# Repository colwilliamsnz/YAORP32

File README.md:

# YAORP32
 
## Yet Another Open Reflow Plate

A design for a solder reflow plate for SMD rework using commonly available aluminium 400W PTC (positive-temperature-coefficient) heating plate from AliExpress. Temperature is
determined using a K type thermocouple and read using a MAX6675/MAX31855. The PTC is driven by an SSR (solid state relay) using PWM and controlled by a PID. An ESP32 S3 Wroom 1 module is at the heart of the design and firmware is written in C++ for Arduino IDE.

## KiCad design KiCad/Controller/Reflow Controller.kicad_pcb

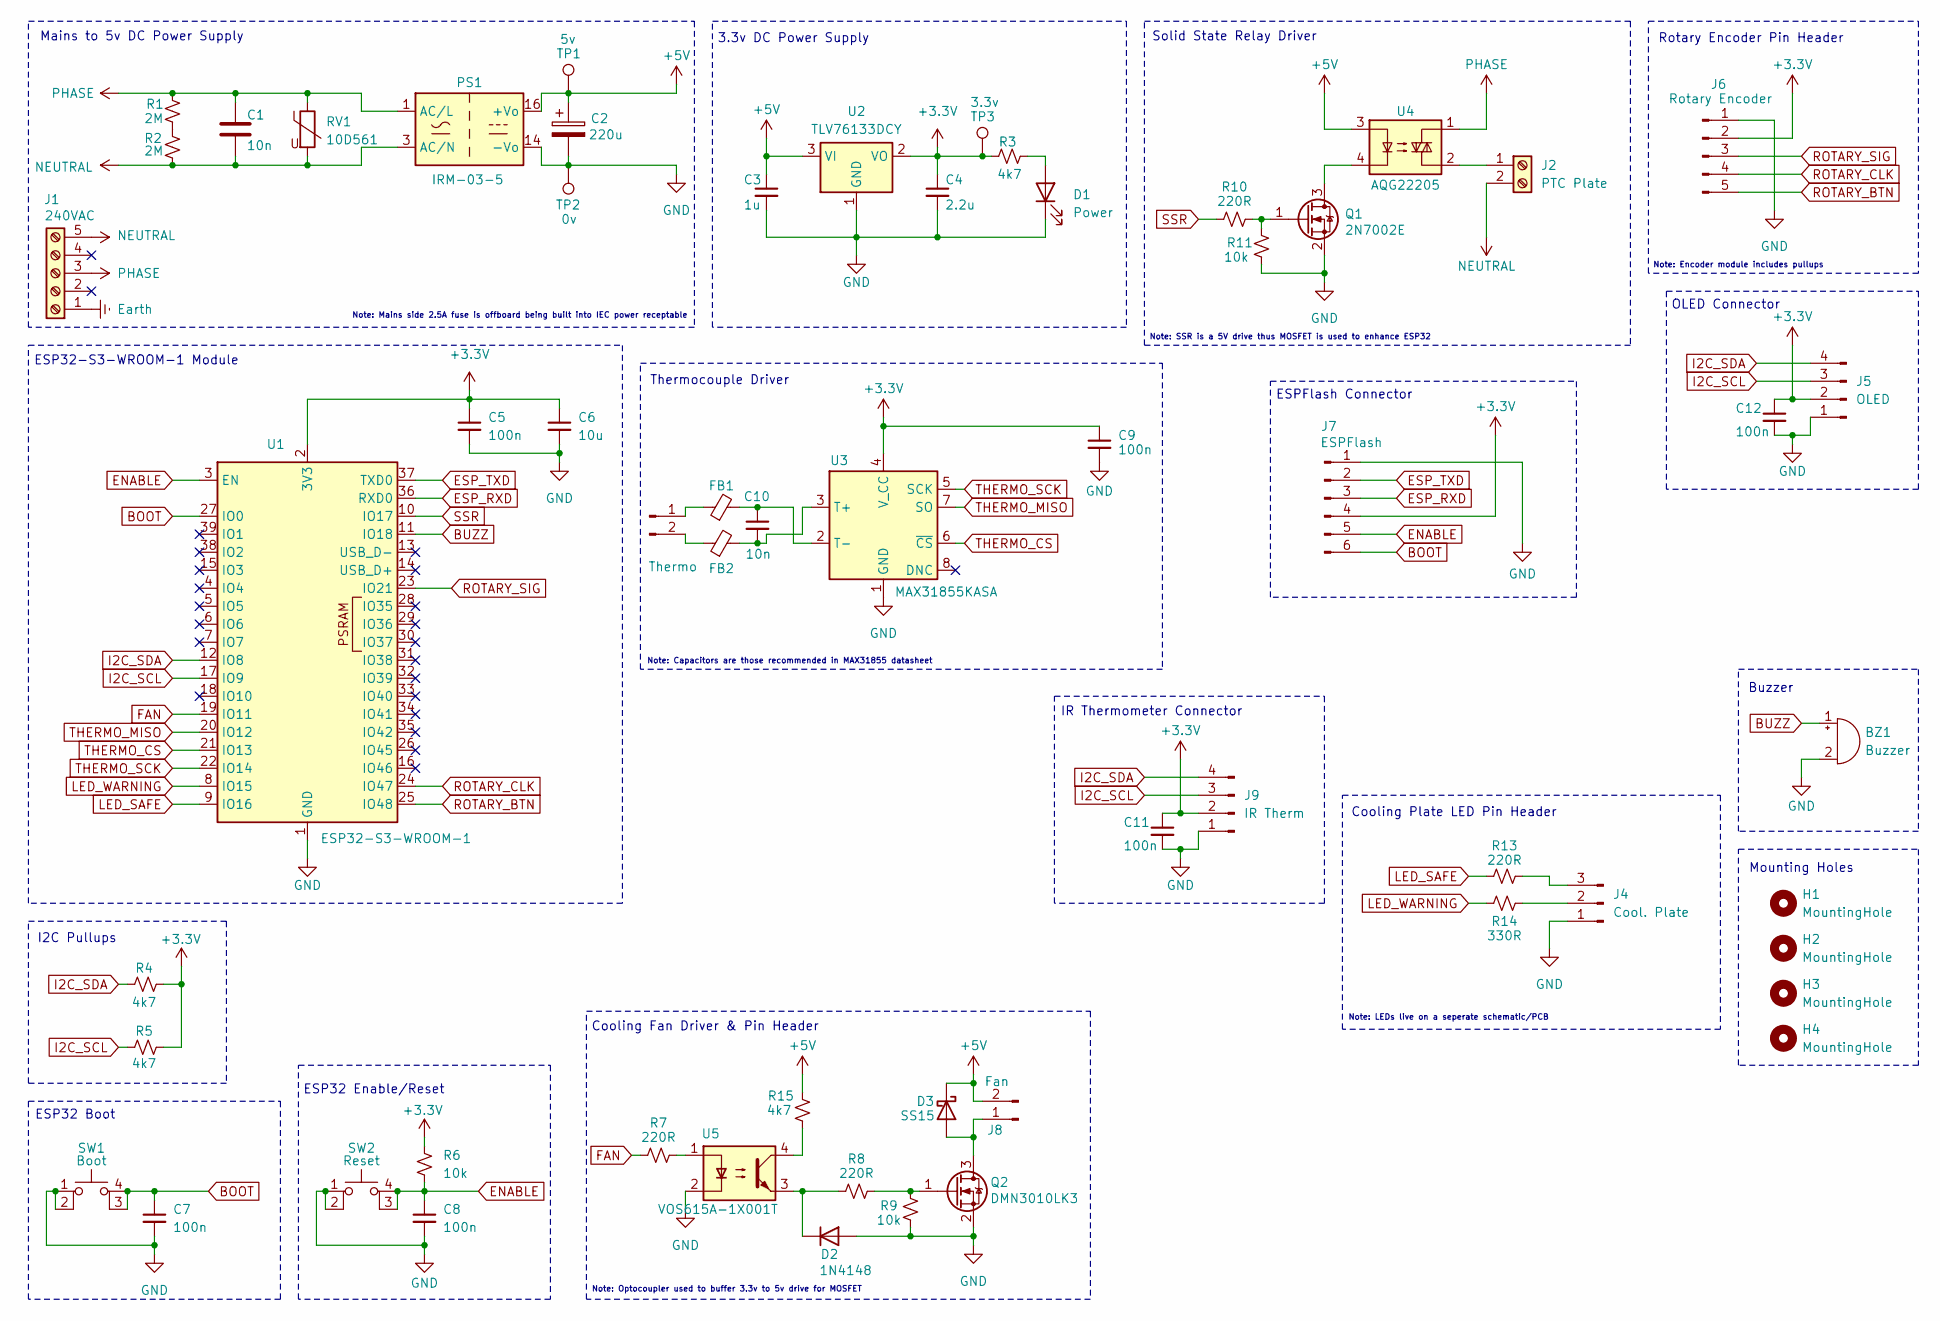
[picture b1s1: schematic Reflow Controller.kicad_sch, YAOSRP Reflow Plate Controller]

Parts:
BZ1: Buzzer; Buzzer_12x9.5RM7.6; Digikey_PN 668-1470-ND
C1: 10n; C_Rect_L18.0mm_W5.0mm_P15.00mm_FKS3_FKP3
C2: 220u; CP_Radial_D6.3mm_P2.50mm
C3: 1u; C_0603_1608Metric; Digikey_PN 1276-1019-1-ND
C4: 2.2u; C_0603_1608Metric; Digikey_PN 1276-1040-1-ND
C5, C7, C8, C9, C11, C12: 100n; C_0603_1608Metric; Digikey_PN 399-C0603C104K4RACTUCT-ND
C6: 10u; C_0805_2012Metric; Digikey_PN 490-6473-1-ND
C10: 10n; C_0603_1608Metric; Digikey_PN 311-3369-1-ND
D1: Power; LED_0603_1608Metric; Digikey_PN 732-4978-1-ND
D2: 1N4148; Nexperia_CFP3_SOD-123W; Digikey_PN 1N4148W-FDICT-ND
D3: SS15; D_SMA; Digikey_PN SS15FSCT-ND
FB1, FB2: 470R 1LN; R_0603_1608Metric; Digikey_PN BLM18PG471SN1D
H1, H2, H3, H4: MountingHole; MountingHole_2.5mm
J1: 240VAC; Altech_AK100_1x05_P5.00mm
J2: PTC Plate; Altech_AK100_1x02_P5.00mm
J3: Thermo; PinHeader_1x02_P2.54mm_Vertical
J4: Cool. Plate; PinHeader_1x03_P2.54mm_Vertical
J5: OLED; PinHeader_1x04_P2.54mm_Vertical
J6: Rotary Encoder; PinHeader_1x05_P2.54mm_Vertical
J7: ESPFlash; PinHeader_1x06_P2.54mm_Vertical
J8: Fan; PinHeader_1x02_P2.54mm_Vertical
J9: IR Therm; PinHeader_1x04_P2.54mm_Vertical
PS1: IRM-03-5; Converter_ACDC_MeanWell_IRM-03-xx_THT; Digikey_PN 1866-3020-ND
Q1: 2N7002E; SOT-23; Digikey_PN 2N7002E-ND
Q2: DMN3010LK3; TO-252-2; Digikey_PN 31-DMN3010LK3-13CT-ND
R1, R2: 2M; R_2010_5025Metric_Pad1.40x2.65mm_HandSolder; Digikey_PN 2019-HV732HTTE2004FCT-ND
R3, R4, R5, R15: 4k7; R_0603_1608Metric_Pad0.98x0.95mm_HandSolder; Digikey_PN 541-3993-1-ND
R6, R9, R11: 10k; R_0603_1608Metric_Pad0.98x0.95mm_HandSolder; Digikey_PN 541-10.0KHCT-ND
R7, R8, R10, R13: 220R; R_0603_1608Metric_Pad0.98x0.95mm_HandSolder; Digikey_PN 541-10440-1-ND
R14: 330R; R_0603_1608Metric_Pad0.98x0.95mm_HandSolder; Digikey_PN 541-10456-1-ND
RV1: 10D561; RV_Disc_D12mm_W6.1mm_P7.5mm; Digikey_PN 118-MOV-10D561K-ND
SW1: Boot; SW_SPST_PTS810; Digikey_PN CKN10878CT-ND
SW2: Reset; SW_SPST_PTS810; Digikey_PN CKN10878CT-ND
TP1: 5v; TestPoint_Pad_D1.0mm
TP2: 0v; TestPoint_Pad_D1.0mm
TP3: 3.3v; TestPoint_Pad_D1.0mm
U1: ESP32-S3-WROOM-1; Digikey_PN 1965-ESP32-S3-WROOM-1-N4R2CT-ND
U2: TLV76133DCY; SOT-223-3_TabPin2; Digikey_PN 296-TLV76133DCYRCT-ND
U3: MAX31855KASA; SOIC-8_3.9x4.9mm_P1.27mm; Digikey_PN MAX31855KASA+-ND
U4: AQG22205; SSR_AQG22105; Digikey_PN 255-3752-ND
U5: VOS615A-1X001T; SSOP-4_4.4x2.6mm_P1.27mm; Digikey_PN 751-VOS615A-1X001TCT-ND

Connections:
+3.3V: C4.1, C5.1, C6.1, C9.1, C11.1, C12.1, J5.2, J6.2, J7.4, J9.2, R3.1, R4.1, R5.1, R6.2, TP3.1, U1.2 (3V3), U2.2 (VO), U3.4 (V_CC)
+5V: C2.1, C3.1, D3.1 (K), J8.2, PS1.16 (+Vo), R15.1, TP1.1, U2.3 (VI), U4.3
BOOT: C7.1, J7.6, SW1.3 (K), SW1.4 (A), U1.27 (IO0)
BUZZ: BZ1.1 (+), U1.11 (IO18)
ENABLE: C8.1, J7.5, R6.1, SW2.3 (K), SW2.4 (A), U1.3 (EN)
ESP_RXD: J7.3, U1.36 (RXD0)
ESP_TXD: J7.2, U1.37 (TXD0)
Earth: J1.1
FAN: R7.2, U1.19 (IO11)
GND: BZ1.2 (-), C2.2, C3.2, C4.2, C5.2, C6.2, C7.2, C8.2, C9.2, C11.2, C12.2, D1.1 (K), D2.2 (A), J4.1, J5.1, J6.1, J7.1, J9.1, PS1.14 (-Vo), Q1.2 (S), Q2.2 (S), R9.2, R11.2, SW1.1, SW1.2, SW2.1, SW2.2, TP2.1, U1.1 (GND), U1.40 (GND), U1.41 (GND), U2.1 (GND), U3.1 (GND), U5.2
I2C_SCL: J5.3, J9.3, R5.2, U1.17 (IO9)
I2C_SDA: J5.4, J9.4, R4.2, U1.12 (IO8)
LED_SAFE: R13.2, U1.9 (IO16)
LED_WARNING: R14.2, U1.8 (IO15)
NEUTRAL: C1.2, J1.5, J2.2, PS1.3 (AC/N), R2.2, RV1.2
unnamed: D1.2 (A), R3.2
unnamed: D2.1 (K), R8.2, U5.3
unnamed: D3.2 (A), J8.1, Q2.3 (D)
unnamed: J2.1, U4.2
unnamed: FB1.1, J3.1
unnamed: FB2.1, J3.2
unnamed: J4.2, R14.1
unnamed: J4.3, R13.1
unnamed: Q1.3 (D), U4.4
unnamed: Q1.1 (G), R10.1, R11.1
unnamed: Q2.1 (G), R8.1, R9.1
unnamed: R1.2, R2.1
unnamed: R7.1, U5.1
unnamed: R15.2, U5.4
unnamed: C10.2, FB2.2, U3.3 (T+)
unnamed: C10.1, FB1.2, U3.2 (T-)
PHASE: C1.1, J1.3, PS1.1 (AC/L), R1.1, RV1.1, U4.1
ROTARY_BTN: J6.5, U1.25 (IO48)
ROTARY_CLK: J6.4, U1.24 (IO47)
ROTARY_SIG: J6.3, U1.23 (IO21)
SSR: R10.2, U1.10 (IO17)
THERMO_CS: U1.21 (IO13), U3.6 (~CS)
THERMO_MISO: U1.20 (IO12), U3.7 (SO)
THERMO_SCK: U1.22 (IO14), U3.5 (SCK)

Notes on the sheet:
Cooling Fan Driver & Pin Header
Thermocouple Driver
Solid State Relay Driver
ESP32 Boot
Buzzer
Note: Capacitors are those recommended in MAX31855 datasheet
Rotary Encoder Pin Header
3.3v DC Power Supply
Note: Optocoupler used to buffer 3.3v to 5v drive for MOSFET
ESP32-S3-WROOM-1 Module
I2C Pullups
ESPFlash Connector
Note: SSR is a 5V drive thus MOSFET is used to enhance ESP32
ESP32 Enable/Reset
Mounting Holes
Note: Mains side 2.5A fuse is offboard being built into IEC power receptable
Mains to 5v DC Power Supply
Cooling Plate LED Pin Header
Note: LEDs live on a seperate schematic/PCB
Note: Encoder module includes pullups
OLED Connector
IR Thermometer Connector

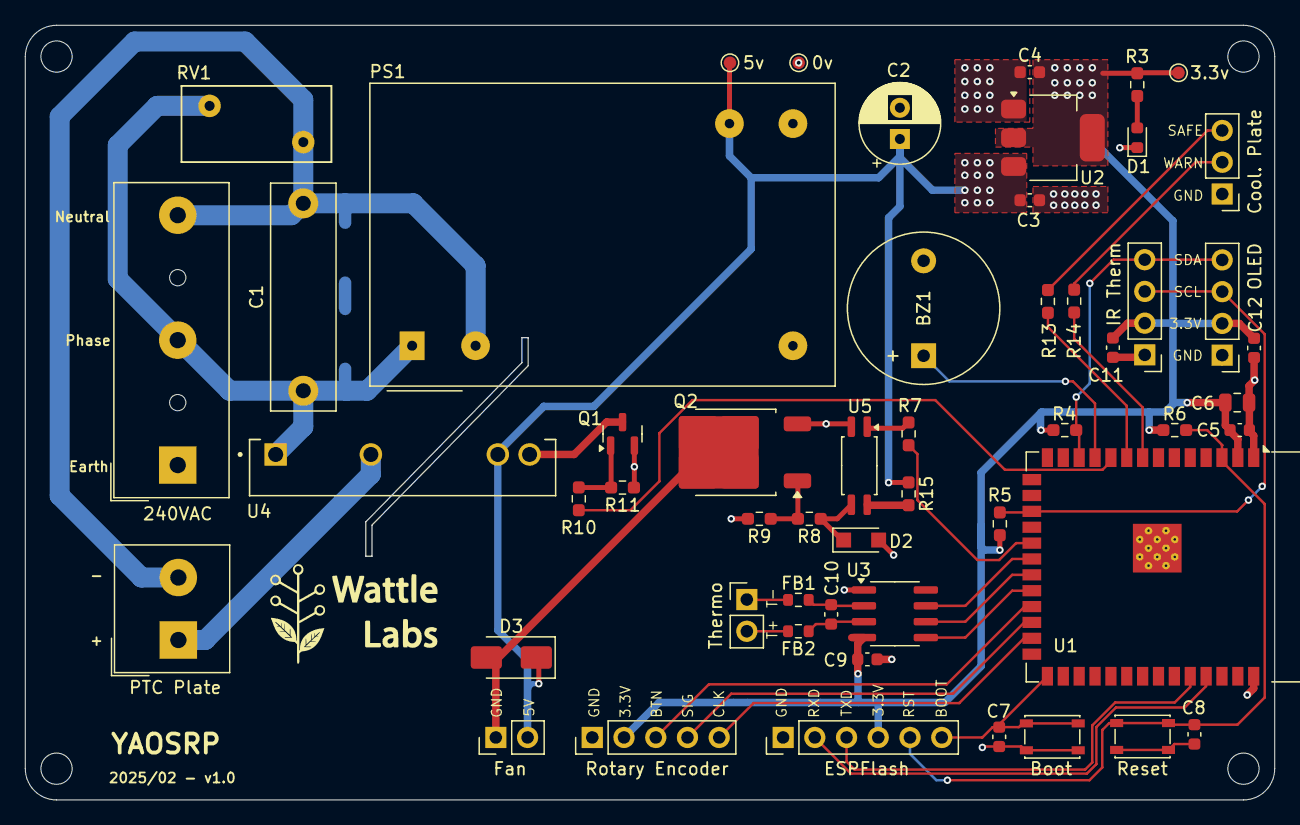
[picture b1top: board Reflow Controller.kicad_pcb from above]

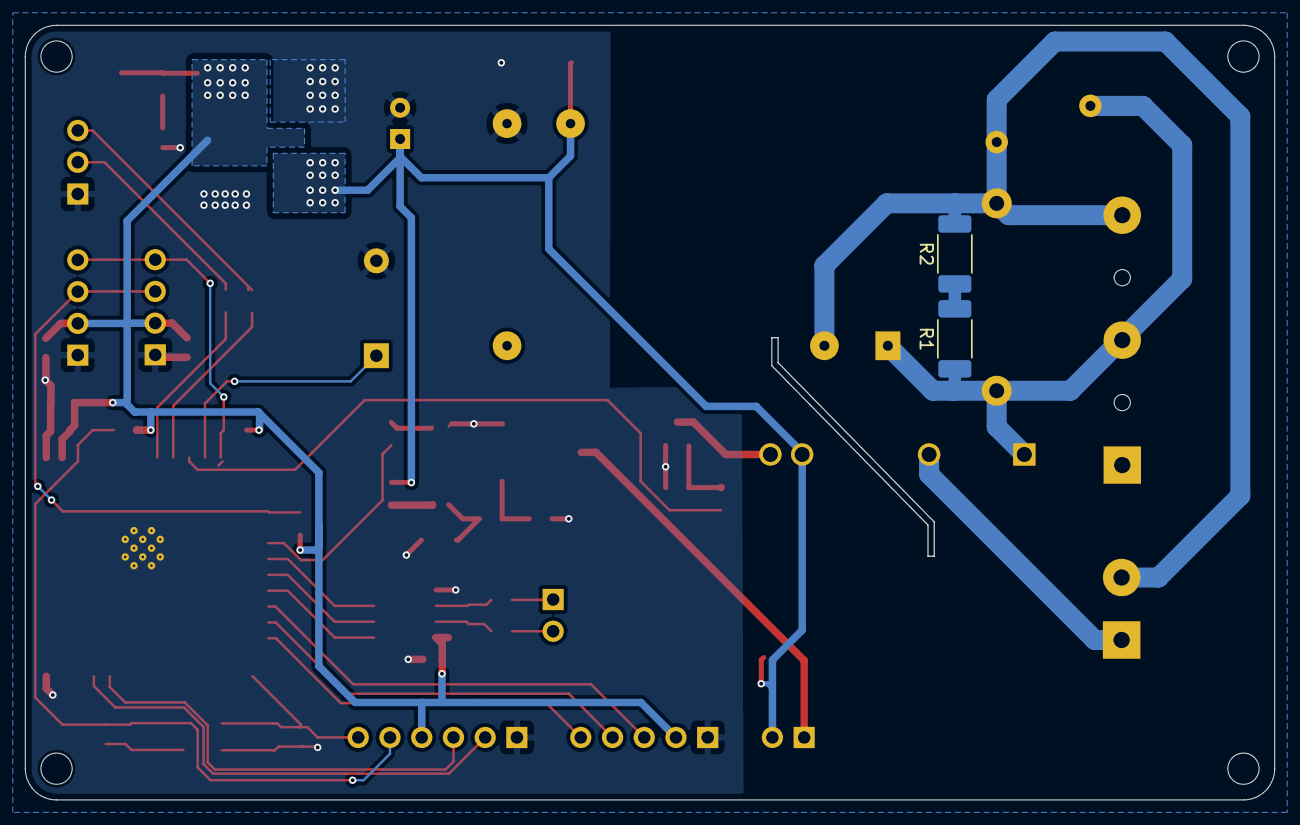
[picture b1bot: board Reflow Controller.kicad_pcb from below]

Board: 4 copper layers, 100.0 x 62.0 mm, 59 parts (2 on the bottom side), 38 nets.

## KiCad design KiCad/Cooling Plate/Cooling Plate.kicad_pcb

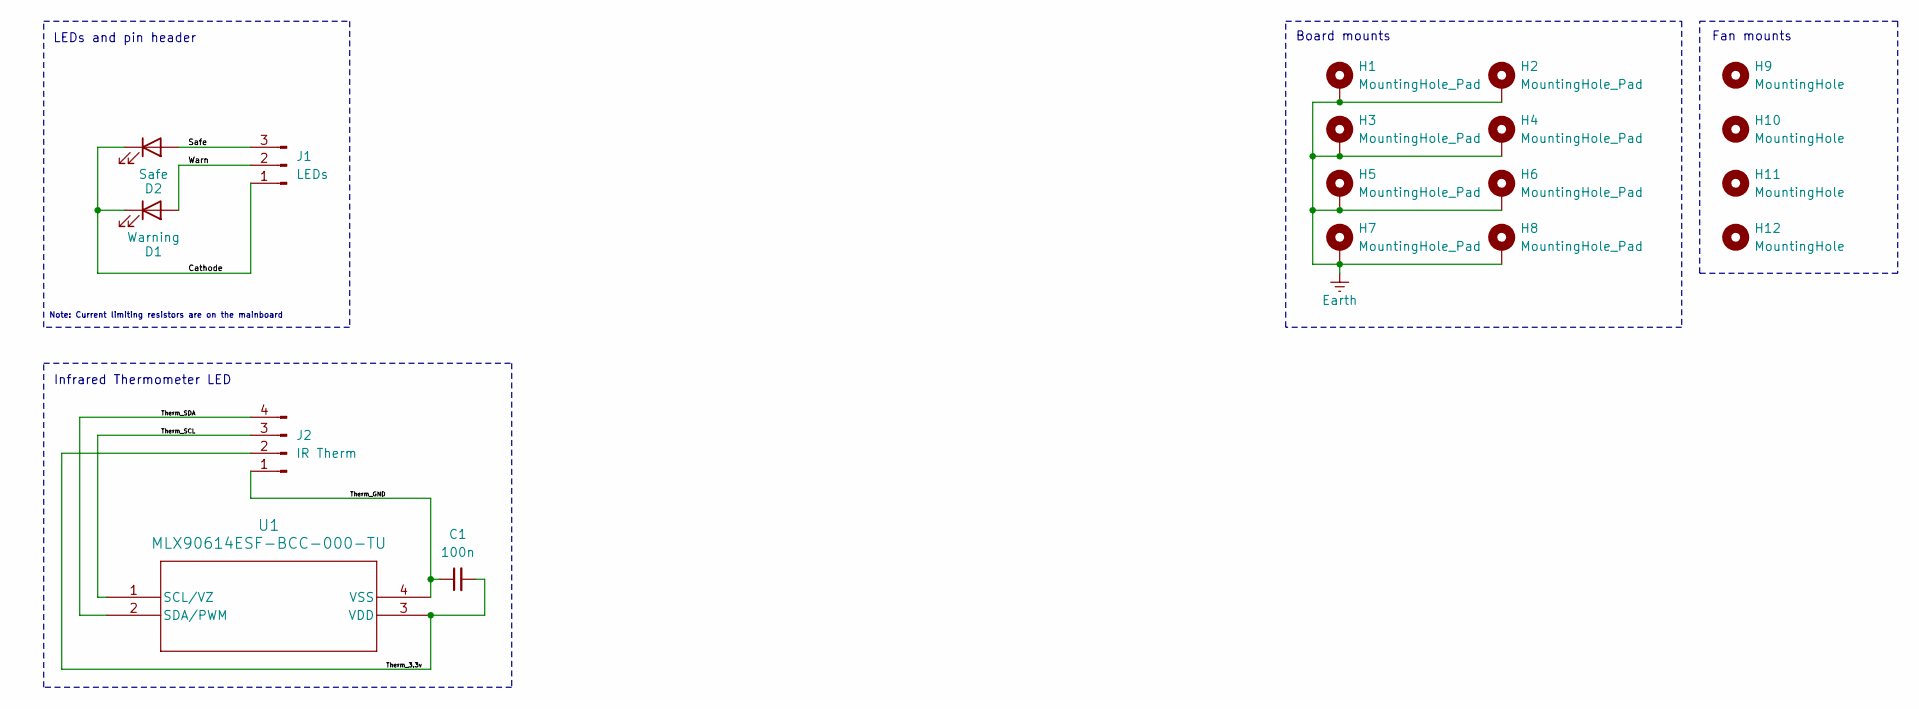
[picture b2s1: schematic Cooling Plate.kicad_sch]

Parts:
C1: 100n; C_0603_1608Metric; Digikey_PN CC0603KRX7R7BB104
D1: Warning; LED_D3.0mm
D2: Safe; LED_D3.0mm
H1, H2, H3, H4, H5, H6, H7, H8: MountingHole_Pad; MountingHole_2.5mm_Pad_TopBottom
H9, H10, H11, H12: MountingHole; MountingHole_2.5mm
J1: LEDs; PinHeader_1x03_P2.54mm_Horizontal
J2: IR Therm; PinHeader_1x04_P2.54mm_Horizontal
U1: MLX90614ESF-BCC-000-TU; MLX90614xCC_MEL; Digikey_PN MLX90614ESF-BCC-000-TU-ND

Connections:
/Cathode: D1.1 (K), D2.1 (K), J1.1
/Safe: D2.2 (A), J1.3
/Therm_3.3v: C1.2, J2.2, U1.3 (VDD)
/Therm_GND: C1.1, J2.1, U1.4 (VSS)
/Therm_SCL: J2.3, U1.1 (SCL/VZ)
/Therm_SDA: J2.4, U1.2 (SDA/PWM)
/Warn: D1.2 (A), J1.2
Earth: H1.1, H2.1, H3.1, H4.1, H5.1, H6.1, H7.1, H8.1

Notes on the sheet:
Fan mounts
LEDs and pin header
Note: Current limiting resistors are on the mainboard
Board mounts
Infrared Thermometer LED

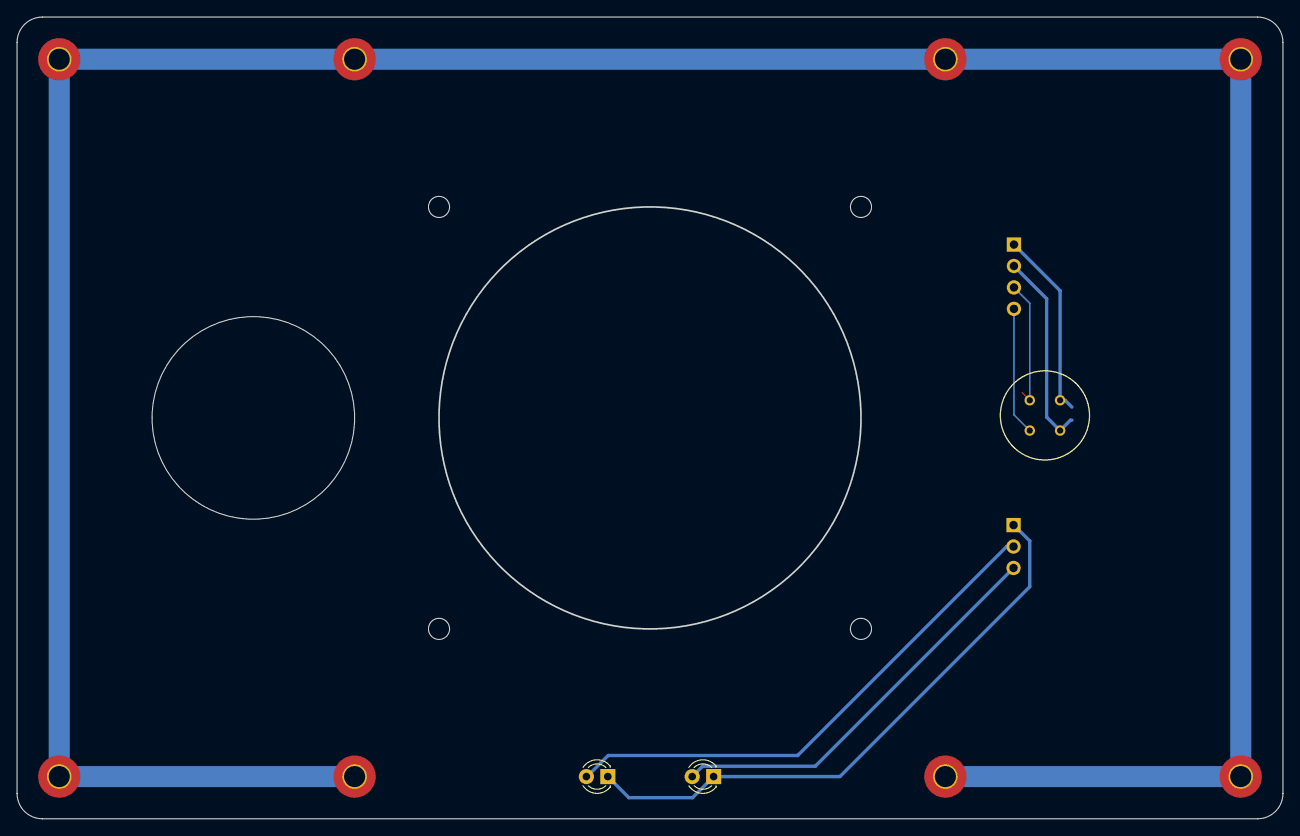
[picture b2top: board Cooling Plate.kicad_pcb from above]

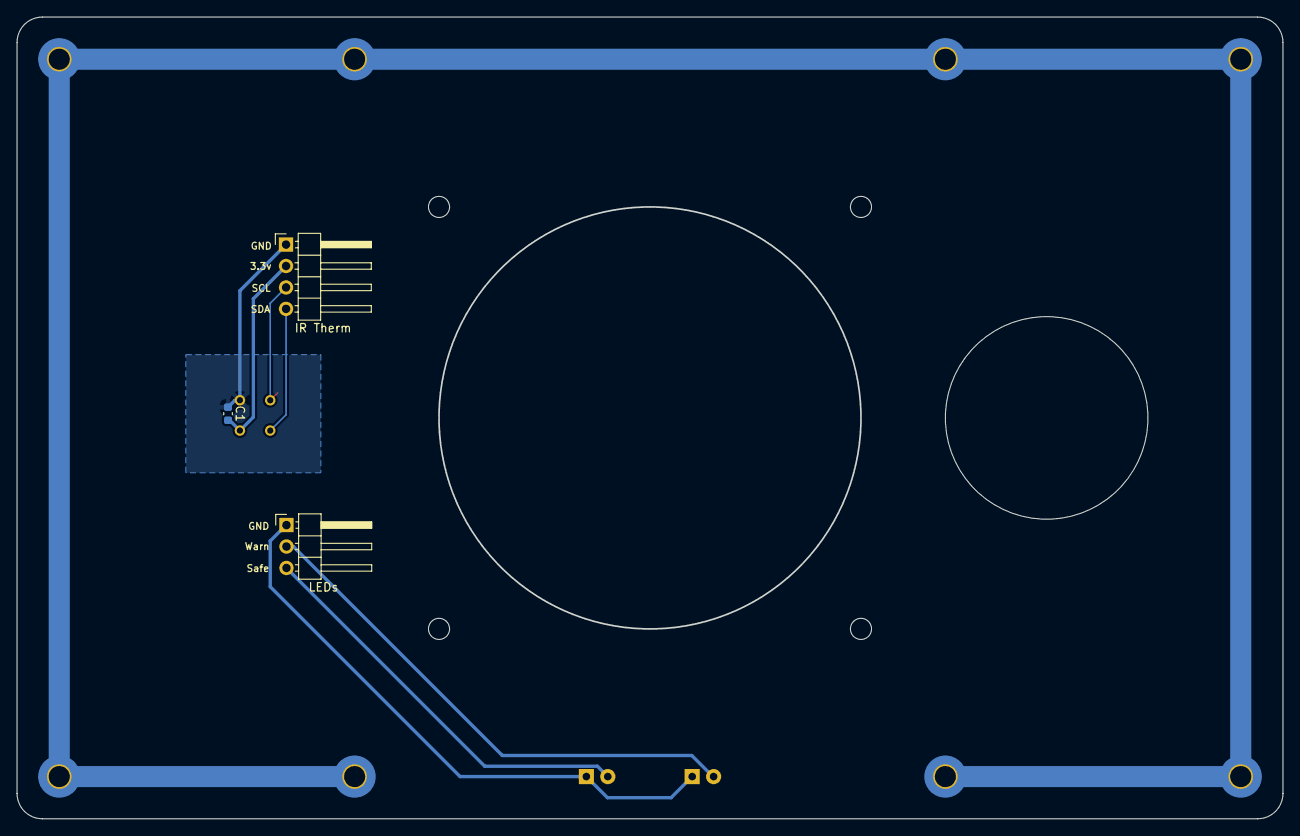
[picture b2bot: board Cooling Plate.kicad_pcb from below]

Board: 2 copper layers, 150.0 x 95.0 mm, 18 parts (3 on the bottom side), 8 nets.

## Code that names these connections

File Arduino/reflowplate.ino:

/* ---================================YAORP32 v0.1 ==================================---
Software to drive Wattle Labs YAORP32 (Yet Another Open Reflow Plate) based on ESP32 S3
and commonly available aluminium 400W PTC heating plates from AliExpress. Temperature is
determined using a K type thermocouple and read using a MAX6675. The PTC is driven by an
SSR using PWM and controlled by a PID.

Initial 0.1 release for testing and circuit board design purposes. Future improvements may
implement selectable reflow curves. For now the reflow temp can be changed in the UI and
the single curve in the code using "temp_preheat" variable.
*/

/* --- To do ---
1. Add confirmation sound(s) when each phase completes. Maybe a pip to represent each phase
2. Add a safety timer that will shutdown the PID/Hotplate if the elapsed time exceeds a value
*/

// Native libraries
#include <Arduino.h>
#include <Wire.h>

#include "driver/ledc.h" // ESP32 library for hardware timers (for LED flashing, and SSR PWM)

// Third party libraries
#include <U8g2lib.h> // Graphics library for OLED screen - https://github.com/olikraus/u8g2
#include "max6675.h" // MAX6675 thermocouple library - https://github.com/adafruit/MAX6675-library
#include <AutoPID.h> // PID libary - https://ryand.io/AutoPID/
#include "avdweb_Switch.h" // Switch library for debounce and hold function - https://github.com/avdwebLibraries/avdweb_Switch
#include <Rotary.h> // Rotary encoder library

// UI image resources
#include "logos.h"

// I2C GPIO connections for OLED display (SSD1306)
#define PIN_I2C_SDA 21
#define PIN_I2C_SCL 22

// Ancillary GPIO connections for SSR, Buzzer, indicator LEDs
#define PIN_SSR 33
#define PIN_BUZZER 27
#define PIN_LED_SAFE 4
#define PIN_LED_WARN 15

// SPI GPIO connections for MAX6675 Thermocouple Converter
#define PIN_THERMO_SDO 19
#define PIN_THERMO_CS 23
#define PIN_THERMO_SCK 5

// Rotary encoder GPIO connections
#define PIN_ROTARY_CLK 14  // rotary encoder CLK pin
#define PIN_ROTARY_SIG 13  // rotary encoder SIG pin
#define PIN_ROTARY_BUT 26  // press and hold button > 1s to "select"

// PID settings and gains
#define OUTPUT_MIN 0
#define OUTPUT_MAX 255
#define KP 2
#define KI .0025
#define KD 9

/* Try these :)
#define KP .12
#define KI .0003
#define KD 0
*/

#define TEMP_READ_DELAY 250    // Delay in ms to take temperature readings. Max6675 allows only every ~250ms
#define SCREEN_DRAW_DELAY 500  // Delay in ms to update the OLED display.

// Variables /////////////////////////////////////////////////////////////////
unsigned long lastTempUpdate;    //tracks time of last temp update
unsigned long lastScreenUpdate;  //tracks time of last screen update
unsigned long lastTimerUpdate;   // tracks timer of last timer update

int timerMode;  // used to track how long to spend in each mode once temperature is reached by the PID

double temperature, setTemp, outputVal;
double temp_preheat = 150;
double temp_reflow = 200;
int mode;  // 0 = Idle, 1 = Preheat, 2 = Soak, 3 = Reflow
int screen;
char *modeDescription = "";

bool boolAtSetPoint = false;
/////////////////////////////////////////////////////////////////////////////

// Instansiate SSD1306 display object
U8G2_SSD1306_128X64_NONAME_F_HW_I2C u8g2(U8G2_R0, PIN_I2C_SCL, PIN_I2C_SDA, U8X8_PIN_NONE);

// Instantiate MAX6675 thermocouple object
MAX6675 thermocouple(PIN_THERMO_SCK, PIN_THERMO_CS, PIN_THERMO_SDO);

// Instantiate AutoPID object
// input/output variables passed by reference, so they are updated automatically
AutoPID myPID(&temperature, &setTemp, &outputVal, OUTPUT_MIN, OUTPUT_MAX, KP, KI, KD);

// Instantiate rotary encoder rotation detection/debounce object - library "Rotary"
Rotary rotary = Rotary(PIN_ROTARY_CLK, PIN_ROTARY_SIG);

// Instantiate rotary encoder switch debounce object - library "AVDWeb_Switch"
Switch pushButton = Switch(PIN_ROTARY_BUT, INPUT_PULLUP, LOW, 1);

void setup() {
  Serial.begin(115200);
  Serial.println(F("Debug started..."));

  // Setup ledc channels for PWM control of SSR, warning LEDs, and sound output
  // Note the channel set-up was required to ensure SSR PWM freq. = 1kHz. Any other channels resulted in 1Hz and disruption of sound output
  ledcAttachChannel(PIN_SSR, /*PWM_FREQUENCY*/ 1000, /*PWM_RESOUTION */8, /*CHANNEL*/ 7); // 1000Hz needed to drive the plate to full temperatures!
  ledcAttachChannel(PIN_LED_WARN, /*PWM_FREQUENCY=*/4, /*PWM_RESOUTION=*/8, 1);  // 4Hz = lowest freq. hardware timer runs at. 8bit means values 0-255. Channel 1.
  ledcAttachChannel(PIN_LED_SAFE, /*PWM_FREQUENCY=*/4, /*PWM_RESOUTION=*/8, 2);
  ledcAttachChannel(PIN_BUZZER, /*PWM_FREQUENCY=*/4, /*PWM_RESOUTION=*/8, 4);

  // Setup PID
  myPID.setBangBang(30); // Bang bang set to > 30 below setpoint (0 to turn off)
  myPID.setTimeStep(TEMP_READ_DELAY);  // set PID update freq. to same as temperature sensor

  // Ensure status LEDs reflect startup temperature!
  temperature = thermocouple.readCelsius(); // Get plate temperature. We get it directly rather than through the function to mitigate startup delay showing incorrect warning LED status
  updateLEDs(); // Update LEDs based on plate temperature
  
  ui_boot();  // Display boot screen

  disableSSR();  // Ensure the SSR is turned off at boot

  mode = 0;  // Start in idle mode
  screen = 0; // Start in temp monitoring screen
}

void loop() {
  processEncoder(); // Process the rotary encoder

  getTemperature();  // Get temperature from thermocouple

  updateLEDs();  // Update LEDs based on plate temperature

  updateUI();  // Draw appropriate screen

  processModes(); // Pre-heat, soak, reflow...
}

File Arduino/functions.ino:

//call repeatedly in loop, only updates after a certain time interval
//returns true if update happened
bool getTemperature() {
  if ((millis() - lastTempUpdate) > TEMP_READ_DELAY) {
    temperature = thermocouple.readCelsius();
    lastTempUpdate = millis();
    return true;
  }
  return false;
}

void updateTimer() {
  if ((millis() - lastTimerUpdate) > 1000) {
    if (timerMode > 0) {
      timerMode = timerMode - 1;
      lastTimerUpdate = millis();
      Serial.println(timerMode);
    }
  }
}

// Status LEDs
void updateLEDs() {
  if (temperature > 40 && temperature < 80) {
    ledc_stop(LEDC_HIGH_SPEED_MODE, LEDC_CHANNEL_2, 0);  // stop flashing SAFE LED
    ledcWrite(PIN_LED_WARN, 255);                        // set WARN LED to 100% duty cycle
  } else if (temperature > 80) {
    ledc_stop(LEDC_HIGH_SPEED_MODE, LEDC_CHANNEL_2, 0);  // stop flashing WARN LED
    ledcWrite(PIN_LED_WARN, 128);                        // set SAFE LED to 100% duty cycle
  } else {
    ledc_stop(LEDC_HIGH_SPEED_MODE, LEDC_CHANNEL_1, 0);  // stop flashing WARN LED
    ledcWrite(PIN_LED_SAFE, 255);                        // set SAFE LED to 100% duty cycle
  }
}

void disableSSR() {
  setTemp = 0;
  ledc_stop(LEDC_HIGH_SPEED_MODE, LEDC_CHANNEL_7, 0);
}

void updateSSR(double PWM) {
  ledcWrite(PIN_SSR, PWM);
}

void processModes() {
  // Idle
  if (mode == 0) {  // Idle mode
    disableSSR();
    timerMode = 0;
    modeDescription = "Idle";
  }

  // Preheat to soak
  if (mode == 1) {
    modeDescription = "Preheat";
    setTemp = temp_preheat;

    myPID.run();

    updateSSR(outputVal);

    if (myPID.atSetPoint(2)) {
      timerMode = 90;  // start countdown timer 90s
      mode = 2;        // Soak mode
    }
  }

  // Soak
  if (mode == 2) {
    modeDescription = "Soak";

    myPID.run();

    updateSSR(outputVal);

    if (myPID.atSetPoint(2)) {
      boolAtSetPoint = true;  // only start the timer if we reached the setpoint
    }

    if (boolAtSetPoint) {
      updateTimer();
    }

    // Soak countdown timer is complete, move to reflow
    if (timerMode == 0) {
      timerMode = 15;  // start
      mode = 3;        // Reflow mode
      boolAtSetPoint = false;
    }
  }

  // Reflow
  if (mode == 3) {
    modeDescription = "Reflow";
    setTemp = temp_reflow;

    myPID.run();

    updateSSR(outputVal);

    if (myPID.atSetPoint(2)) {
      boolAtSetPoint = true;  // only start the timer if we reached the setpoint
    }

    if (boolAtSetPoint) {
      updateTimer();
    }

    if (timerMode == 0) {  // reflow is finished, revert to idle mode
      mode = 0;
      screen = 0;
      boolAtSetPoint = false;
    }
  }
}

void processEncoder() {
  // Poll rotary encoder and pushbutton /////////////////////////////////////////
  unsigned char result = rotary.process();
  pushButton.poll();

  // process rotary encoder inputs only when in the temperature select screen ///
  if (screen == 1 && result == DIR_CW && (temp_reflow < 220)) {
    temp_reflow += 5;
    soundClick();
  }

  if (screen == 1 && result == DIR_CCW && (temp_reflow > 160)) {
    temp_reflow -= 5;
    soundClick();
  }

  // Process long press as appropriate
  if (pushButton.longPress()) {
    if (screen == 0) {
      screen = 1;
      soundConfirm();
    } else if (screen == 1) {
      screen = 2;
      mode = 1;
      soundConfirm();
    } else if (screen == 2) {
      screen = 0;
      mode = 0;
      soundCancel();
    }
  }
}

void updateUI() {
  if ((millis() - lastScreenUpdate) > SCREEN_DRAW_DELAY) {

    if (screen == 0) {
      ui_idle(temperature);
    }

    if (screen == 1) {
      ui_temp();
    }

    if (screen == 2) {
      ui_heating(modeDescription, setTemp, temperature, timerMode);
    }

    lastScreenUpdate = millis();
  }
}

void soundBoot() {
  // Play startup sound
  ledcWriteTone(PIN_BUZZER, 1000);
  delay(250);
  ledcWriteTone(PIN_BUZZER, 1800);
  delay(180);
  ledcWriteTone(PIN_BUZZER, 0);
}

void soundCancel() {
  // Play cancel sound
  ledcWriteTone(PIN_BUZZER, 1800);
  delay(300);
  ledcWriteTone(PIN_BUZZER, 0);
  delay(50);
  ledcWriteTone(PIN_BUZZER, 1400);
  delay(300);
  ledcWriteTone(PIN_BUZZER, 0);
  delay(50);
  ledcWriteTone(PIN_BUZZER, 1000);
  delay(100);
  ledcWriteTone(PIN_BUZZER, 0);
}

void soundConfirm() {
  ledcWriteTone(PIN_BUZZER, 1800);
  delay(75);
  ledcWriteTone(PIN_BUZZER, 0);
  delay(50);
  ledcWriteTone(PIN_BUZZER, 1800);
  delay(75);
  ledcWriteTone(PIN_BUZZER, 0);
}

void soundClick() {
  ledcWriteTone(PIN_BUZZER, 1800);
  delay(3);
  ledcWriteTone(PIN_BUZZER, 0);
}

void ui_boot() {
  // Render boot screen and play "on" tone from piezo
  u8g2.begin();
  u8g2.enableUTF8Print();

  u8g2.clearBuffer();
  u8g2.setFontMode(1);
  u8g2.setBitmapMode(1);

  u8g2.drawXBMP(12, 0, 37, 64, icon_logo);

  u8g2.setFont(u8g2_font_helvB08_tr);
  u8g2.drawStr(54, 26, "Wattle Labs");
  u8g2.drawStr(57, 41, "YAORP32");

  u8g2.sendBuffer();
  soundBoot();

  delay(2000);
}

void ui_idle(int temp) {
  // Render idle screen showing current plate temperature
  // screen = 1

  char buffer[4] = "";

  u8g2.clearBuffer();
  u8g2.setFontMode(1);
  u8g2.setBitmapMode(1);

  u8g2.setFont(u8g2_font_helvB08_tr);
  u8g2.drawStr(55, 10, "Idle");

  u8g2.drawXBMP(34, 24, 16, 16, icon_temperature);

  itoa(temp, buffer, 10);  // convert int to string

  u8g2.setFont(u8g2_font_profont22_tr);
  u8g2.drawStr(60, 39, buffer);

  u8g2.setFont(u8g2_font_5x8_tr);
  u8g2.drawStr(14, 64, "Hold Select to Start");

  u8g2.sendBuffer();
}

void ui_temp() {
  // Render temperature selection screen
  // screen = 2
  char buffer[4] = "";

  u8g2.clearBuffer();
  u8g2.setFontMode(1);
  u8g2.setBitmapMode(1);

  u8g2.setFont(u8g2_font_helvB08_tr);
  u8g2.drawStr(13, 8, "Select Reflow Temp:");

  u8g2.drawXBMP(34, 24, 16, 16, icon_temperature);

  itoa(temp_reflow, buffer, 10);  // convert int to string

  u8g2.setFont(u8g2_font_profont22_tr);
  u8g2.drawStr(60, 39, buffer);

  u8g2.setFont(u8g2_font_5x8_tr);
  u8g2.drawStr(14, 64, "Hold Select to Start");

  u8g2.sendBuffer();
}

void ui_heating(char *phase, int temp_target, int temp_current, int timer) {
  // Render heating screen showing current phase
  // screen = 3
  char buffer[4] = "";

  u8g2.clearBuffer();
  u8g2.setFontMode(1);
  u8g2.setBitmapMode(1);

  u8g2.setFont(u8g2_font_5x8_tr);
  u8g2.drawStr(12, 64, "Hold Select to Cancel");

  u8g2.drawXBMP(34, 24, 16, 16, icon_temperature);

  itoa(temp_target, buffer, 10);  // convert int to string
  u8g2.setFont(u8g2_font_helvB08_tr);
  u8g2.drawStr(100, 8, "T:");
  u8g2.drawStr(110, 8, buffer);

  if (timer > 0) { // only display a timer if one is active
    itoa(timer, buffer, 10);  // convert int to string
    u8g2.drawStr(58, 8, buffer);
  }

  u8g2.setFont(u8g2_font_helvB08_tr);
  u8g2.drawStr(0, 8, phase);

  itoa(temp_current, buffer, 10);  // convert int to string
  u8g2.setFont(u8g2_font_profont22_tr);
  u8g2.drawStr(60, 39, buffer);

  u8g2.sendBuffer();
}

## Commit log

2025-02-16 Create PDFs
2025-02-16 Upload new board1 schematic
    Split schematic into more hierarchical style to aid in project reuse
